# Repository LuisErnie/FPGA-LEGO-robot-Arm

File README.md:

# FPGA-LEGO-robot-Arm
El presente proyecto consiste en el desarrollo de un sistema de control lógico para un robot manipulador de 4 ejes que permita manipular cada uno de forma independiente. El controlador propuesto es implementado en una **FPGA Altera Cyclone V 5CSEMA5F31C6** integrado en la tarjeta **DE1-SOC** de Terasic junto con una tarjeta diseñada para la lectura de las señales de entrada y control de las señales de potencia para los motores, se utilizan optoaisladores para la separación de la tierra de potencia y tierra lógica.
La implementación del código en VHDL permite la jerarquización de bloques de código que cumplan cada una de las funciones UART, PWM, multiplexor, control de motores, etc. requeridos por el proyecto.

El sistema desarrollo consiste en una tarjeta de interfaz para la FPGA y un panel de control para el operador.

El manipulador fue construido con un Kit de LEGO Mindstorms NXT con 4 grados de libertad cada uno controlado por una implementación independiente en la FPGA, esto para demostrar las ventajas de implementar controladores multieje en una FPGA

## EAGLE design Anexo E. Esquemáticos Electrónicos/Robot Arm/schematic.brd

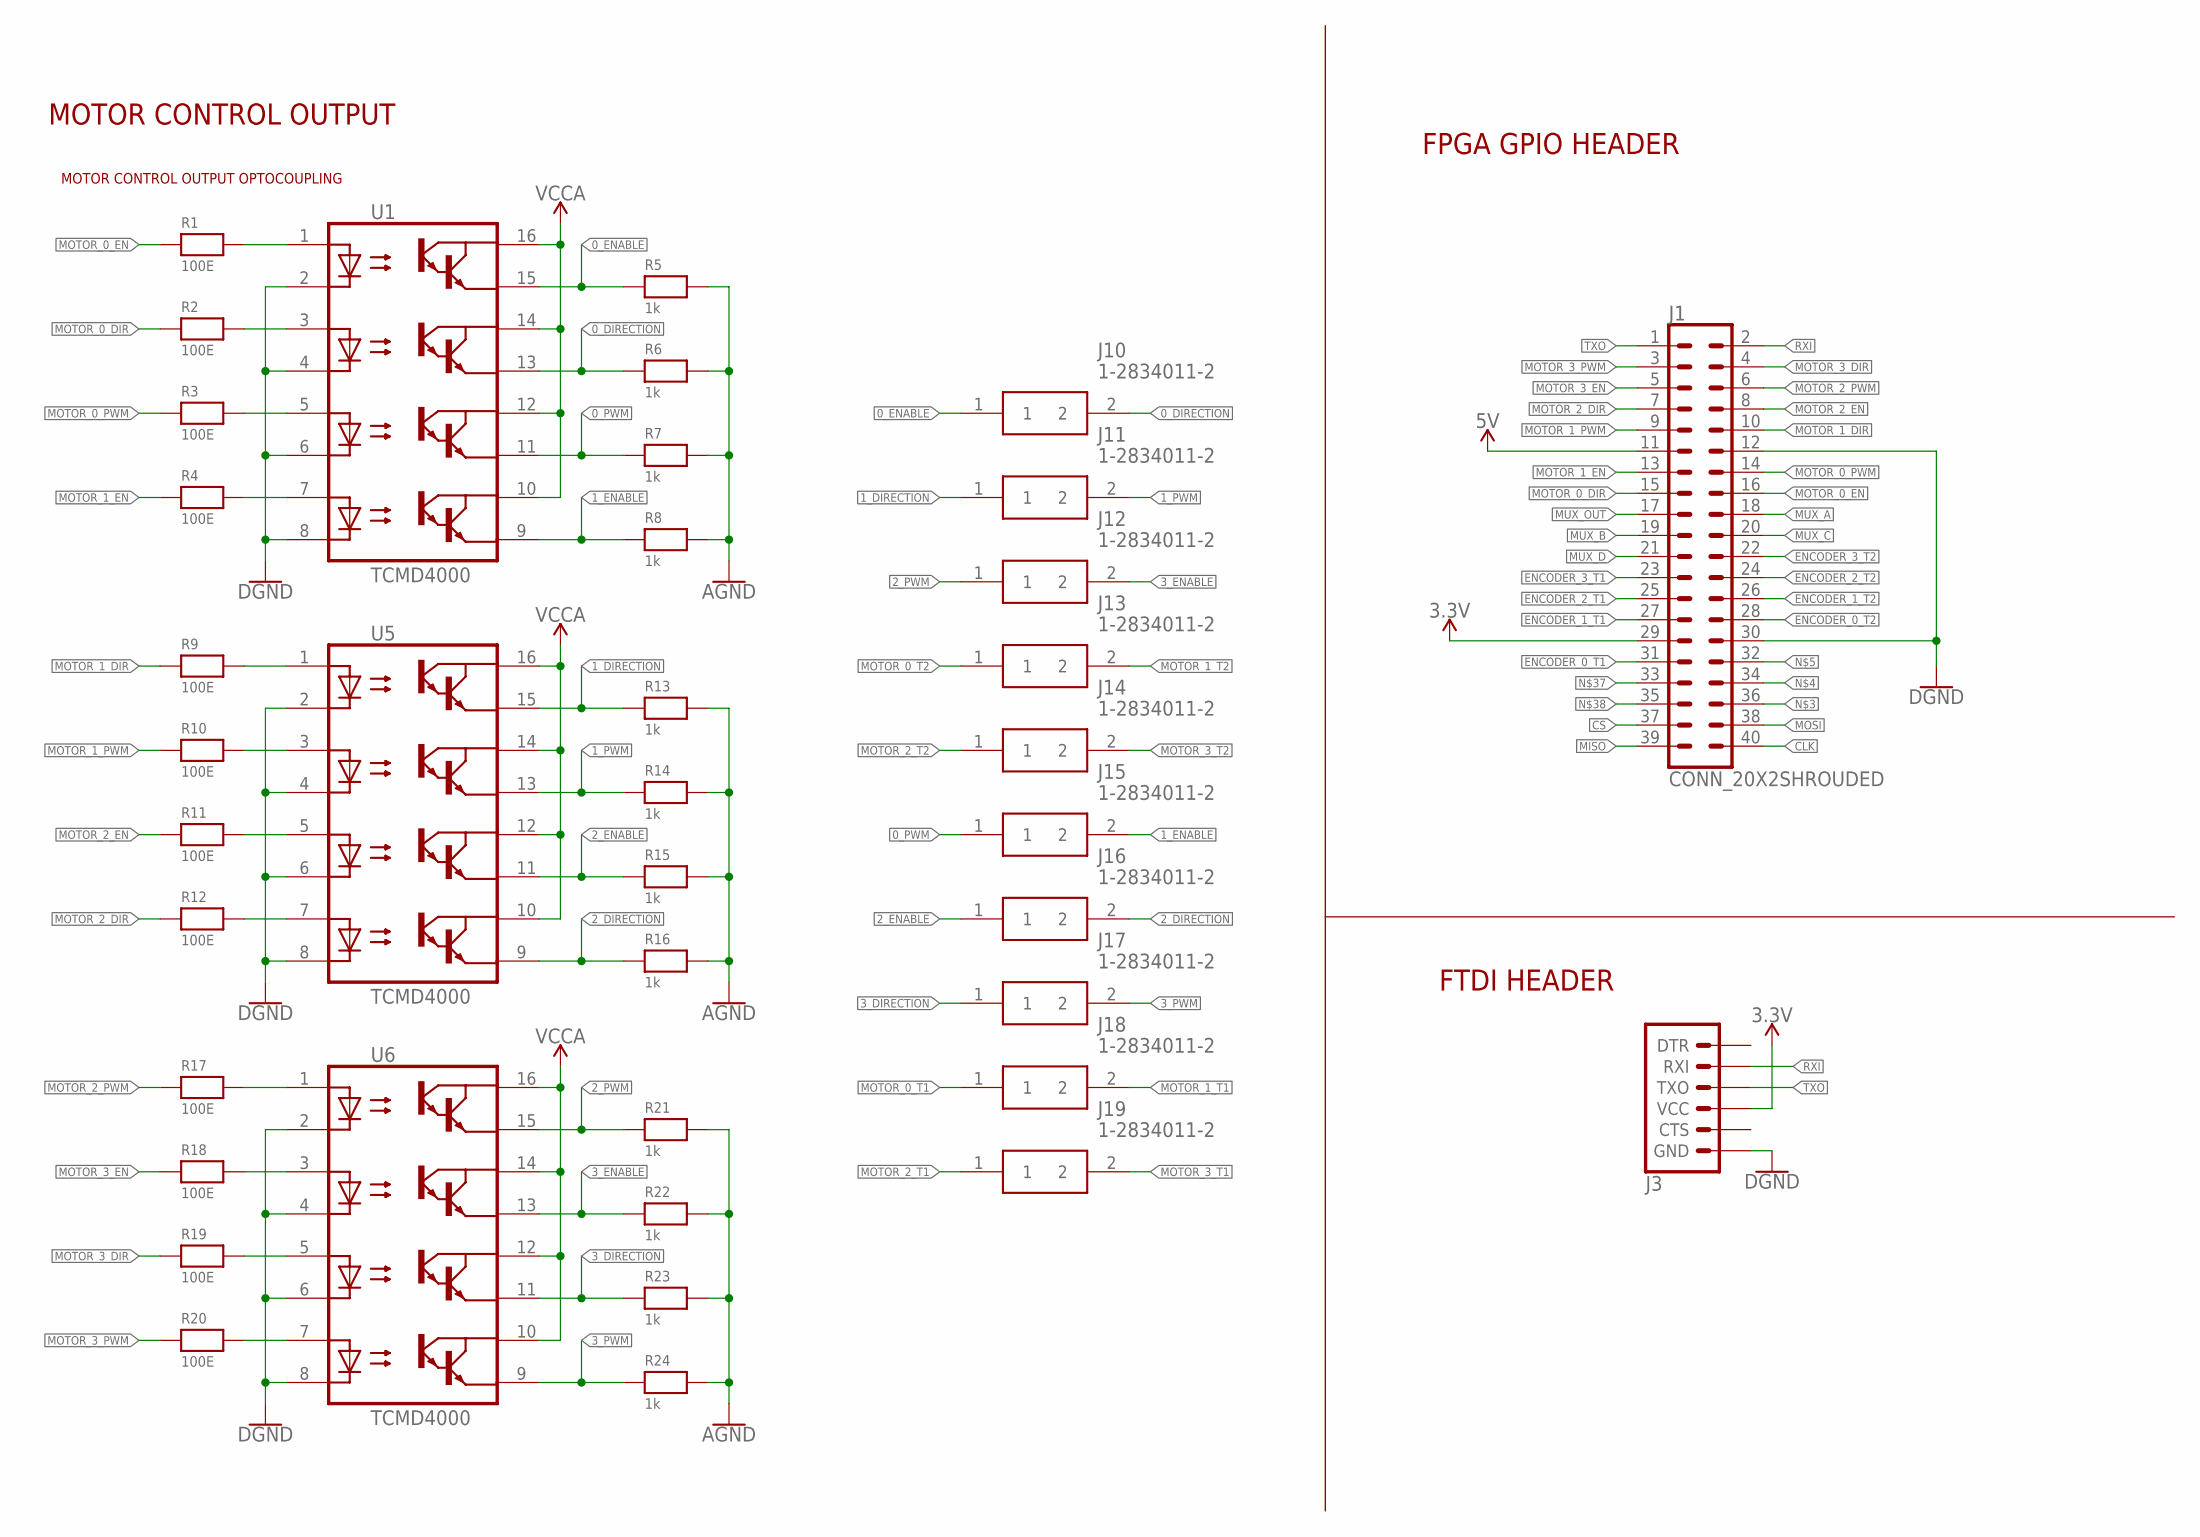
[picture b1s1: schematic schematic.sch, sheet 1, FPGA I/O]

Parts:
J1: CONN_20X2SHROUDED; 2X20_SHROUDED
J3: 6_PIN_SERIAL_TARGET; 1X06
J10, J11, J12, J13, J14, J15, J16, J17, J18, J19: 1-2834011-2; 128340112
R1, R2, R3, R4, R9, R10, R11, R12, R17, R18, R19, R20: 100E; 0805_NOTHERMALS
R5, R6, R7, R8, R13, R14, R15, R16, R21, R22, R23, R24: 1k; 0805_NOTHERMALS
U1, U5, U6: TCMD4000; SOIC127P686X201-16N

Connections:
0_DIRECTION: J10.2, R6.1, U1.13 (E2)
0_ENABLE: J10.1, R5.1, U1.15 (E1)
0_PWM: J15.1, R7.1, U1.11 (E3)
1_DIRECTION: J11.1, R13.1, U5.15 (E1)
1_ENABLE: J15.2, R8.1, U1.9 (E4)
1_PWM: J11.2, R14.1, U5.13 (E2)
2_DIRECTION: J16.2, R16.1, U5.9 (E4)
2_ENABLE: J16.1, R15.1, U5.11 (E3)
2_PWM: J12.1, R21.1, U6.15 (E1)
3.3V: J1.29, J3.4 (VCC); also elsewhere on the board
3_DIRECTION: J17.1, R23.1, U6.11 (E3)
3_ENABLE: J12.2, R22.1, U6.13 (E2)
3_PWM: J17.2, R24.1, U6.9 (E4)
5V: J1.11; also elsewhere on the board
AGND: R5.2, R6.2, R7.2, R8.2, R13.2, R14.2, R15.2, R16.2, R21.2, R22.2, R23.2, R24.2; also elsewhere on the board
CLK: J1.40; also elsewhere on the board
CS: J1.37; also elsewhere on the board
ENCODER_0_T1: J1.31; also elsewhere on the board
ENCODER_0_T2: J1.28; also elsewhere on the board
ENCODER_1_T1: J1.27; also elsewhere on the board
ENCODER_1_T2: J1.26; also elsewhere on the board
ENCODER_2_T1: J1.25; also elsewhere on the board
ENCODER_2_T2: J1.24; also elsewhere on the board
ENCODER_3_T1: J1.23; also elsewhere on the board
ENCODER_3_T2: J1.22; also elsewhere on the board
GND: J1.12, J1.30, J3.6 (GND), U1.2 (C1), U1.4 (C2), U1.6 (C3), U1.8 (C4), U5.2 (C1), U5.4 (C2), U5.6 (C3), U5.8 (C4), U6.2 (C1), U6.4 (C2), U6.6 (C3), U6.8 (C4); also elsewhere on the board
MISO: J1.39; also elsewhere on the board
MOSI: J1.38; also elsewhere on the board
MOTOR_0_DIR: J1.15, R2.1
MOTOR_0_EN: J1.16, R1.1
MOTOR_0_PWM: J1.14, R3.1
MOTOR_0_T1: J18.1; also elsewhere on the board
MOTOR_0_T2: J13.1; also elsewhere on the board
MOTOR_1_DIR: J1.10, R9.1
MOTOR_1_EN: J1.13, R4.1
MOTOR_1_PWM: J1.9, R10.1
MOTOR_1_T1: J18.2; also elsewhere on the board
MOTOR_1_T2: J13.2; also elsewhere on the board
MOTOR_2_DIR: J1.7, R12.1
MOTOR_2_EN: J1.8, R11.1
MOTOR_2_PWM: J1.6, R17.1
MOTOR_2_T1: J19.1; also elsewhere on the board
MOTOR_2_T2: J14.1; also elsewhere on the board
MOTOR_3_DIR: J1.4, R19.1
MOTOR_3_EN: J1.5, R18.1
MOTOR_3_PWM: J1.3, R20.1
MOTOR_3_T1: J19.2; also elsewhere on the board
MOTOR_3_T2: J14.2; also elsewhere on the board
MUX_A: J1.18; also elsewhere on the board
MUX_B: J1.19; also elsewhere on the board
MUX_C: J1.20; also elsewhere on the board
MUX_D: J1.21; also elsewhere on the board
MUX_OUT: J1.17; also elsewhere on the board
unnamed: R1.2, U1.1 (A1)
unnamed: R2.2, U1.3 (A2)
unnamed: R3.2, U1.5 (A3)
unnamed: R4.2, U1.7 (A4)
unnamed: R9.2, U5.1 (A1)
unnamed: R10.2, U5.3 (A2)
unnamed: R11.2, U5.5 (A3)
unnamed: R12.2, U5.7 (A4)
unnamed: R17.2, U6.1 (A1)
unnamed: R18.2, U6.3 (A2)
unnamed: R19.2, U6.5 (A3)
unnamed: R20.2, U6.7 (A4)
RXI: J1.2, J3.2 (RXI)
TXO: J1.1, J3.3 (TXO)
VCCA: U1.10 (CO4), U1.12 (CO3), U1.14 (CO2), U1.16 (CO1), U5.10 (CO4), U5.12 (CO3), U5.14 (CO2), U5.16 (CO1), U6.10 (CO4), U6.12 (CO3), U6.14 (CO2), U6.16 (CO1); also elsewhere on the board

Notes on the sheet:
MOTOR CONTROL OUTPUT
MOTOR CONTROL OUTPUT OPTOCOUPLING
FPGA GPIO HEADER
FTDI HEADER

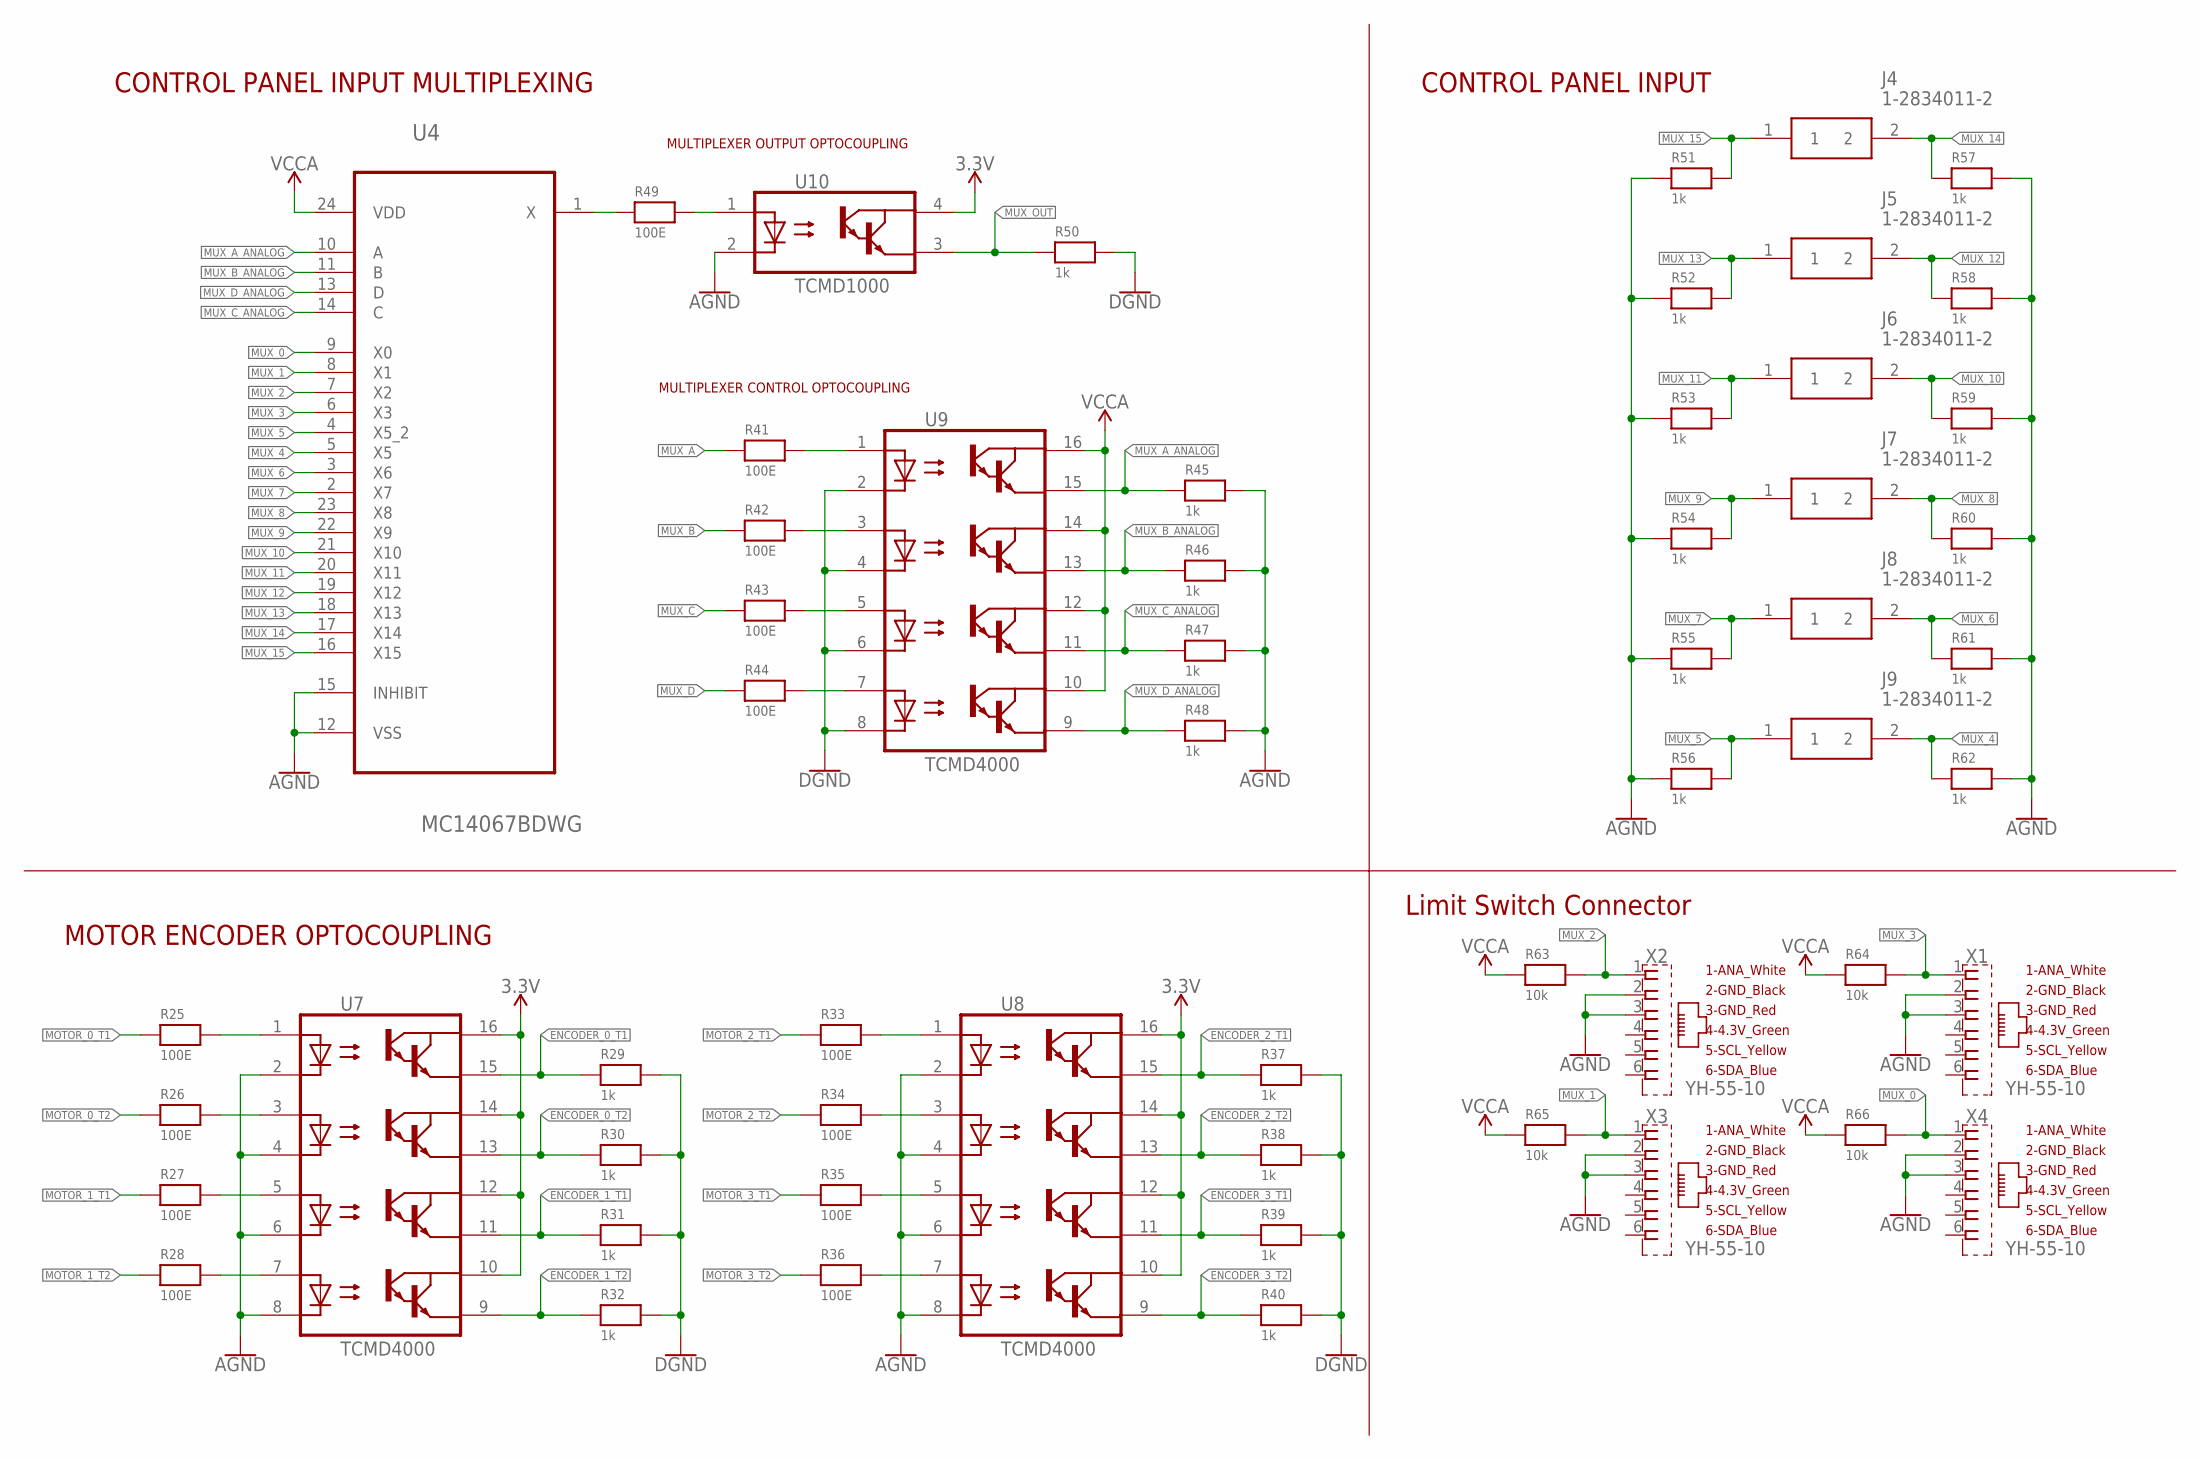
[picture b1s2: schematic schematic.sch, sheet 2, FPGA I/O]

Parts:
J4, J5, J6, J7, J8, J9: 1-2834011-2; 128340112
R25, R26, R27, R28, R33, R34, R35, R36, R41, R42, R43, R44, R49: 100E; 0805_NOTHERMALS
R29, R30, R31, R32, R37, R38, R39, R40, R45, R46, R47, R48, R50, R51, R52, R53, R54, R55, R56, R57, R58, R59, R60, R61, R62: 1k; 0805_NOTHERMALS
R63, R64, R65, R66: 10k; 0805_NOTHERMALS
U4: MC14067BDWG; SOIC127P1030X265-24N
U7, U8, U9: TCMD4000; SOIC127P686X201-16N
U10: TCMD1000; SOIC254P695X210-4N
X1, X2, X3, X4: YH-55-10

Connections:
3.3V: U7.10 (CO4), U7.12 (CO3), U7.14 (CO2), U7.16 (CO1), U8.10 (CO4), U8.12 (CO3), U8.14 (CO2), U8.16 (CO1), U10.4 (CO1); also elsewhere on the board
AGND: R45.2, R46.2, R47.2, R48.2, R51.1, R52.1, R53.1, R54.1, R55.1, R56.1, R57.2, R58.2, R59.2, R60.2, R61.2, R62.2, U4.12 (VSS), U4.15 (INHIBIT), U7.2 (C1), U7.4 (C2), U7.6 (C3), U7.8 (C4), U8.2 (C1), U8.4 (C2), U8.6 (C3), U8.8 (C4), U10.2 (C1), X1.2 (2_GND_BLACK), X1.3 (3_GND_RED), X2.2 (2_GND_BLACK), X2.3 (3_GND_RED), X3.2 (2_GND_BLACK), X3.3 (3_GND_RED), X4.2 (2_GND_BLACK), X4.3 (3_GND_RED); also elsewhere on the board
ENCODER_0_T1: R29.1, U7.15 (E1); also elsewhere on the board
ENCODER_0_T2: R30.1, U7.13 (E2); also elsewhere on the board
ENCODER_1_T1: R31.1, U7.11 (E3); also elsewhere on the board
ENCODER_1_T2: R32.1, U7.9 (E4); also elsewhere on the board
ENCODER_2_T1: R37.1, U8.15 (E1); also elsewhere on the board
ENCODER_2_T2: R38.1, U8.13 (E2); also elsewhere on the board
ENCODER_3_T1: R39.1, U8.11 (E3); also elsewhere on the board
ENCODER_3_T2: R40.1, U8.9 (E4); also elsewhere on the board
GND: R29.2, R30.2, R31.2, R32.2, R37.2, R38.2, R39.2, R40.2, R50.2, U9.2 (C1), U9.4 (C2), U9.6 (C3), U9.8 (C4); also elsewhere on the board
MOTOR_0_T1: R25.1; also elsewhere on the board
MOTOR_0_T2: R26.1; also elsewhere on the board
MOTOR_1_T1: R27.1; also elsewhere on the board
MOTOR_1_T2: R28.1; also elsewhere on the board
MOTOR_2_T1: R33.1; also elsewhere on the board
MOTOR_2_T2: R34.1; also elsewhere on the board
MOTOR_3_T1: R35.1; also elsewhere on the board
MOTOR_3_T2: R36.1; also elsewhere on the board
MUX_0: R66.2, U4.9 (X0), X4.1 (1_ANA_WHITE)
MUX_1: R65.2, U4.8 (X1), X3.1 (1_ANA_WHITE)
MUX_2: R63.2, U4.7 (X2), X2.1 (1_ANA_WHITE)
MUX_3: R64.2, U4.6 (X3), X1.1 (1_ANA_WHITE)
MUX_4: J9.2, R62.1, U4.5 (X5)
MUX_5: J9.1, R56.2, U4.4 (X5_2)
MUX_6: J8.2, R61.1, U4.3 (X6)
MUX_7: J8.1, R55.2, U4.2 (X7)
MUX_8: J7.2, R60.1, U4.23 (X8)
MUX_9: J7.1, R54.2, U4.22 (X9)
MUX_10: J6.2, R59.1, U4.21 (X10)
MUX_11: J6.1, R53.2, U4.20 (X11)
MUX_12: J5.2, R58.1, U4.19 (X12)
MUX_13: J5.1, R52.2, U4.18 (X13)
MUX_14: J4.2, R57.1, U4.17 (X14)
MUX_15: J4.1, R51.2, U4.16 (X15)
MUX_A: R41.1; also elsewhere on the board
MUX_A_ANALOG: R45.1, U4.10 (A), U9.15 (E1)
MUX_B: R42.1; also elsewhere on the board
MUX_B_ANALOG: R46.1, U4.11 (B), U9.13 (E2)
MUX_C: R43.1; also elsewhere on the board
MUX_C_ANALOG: R47.1, U4.14 (C), U9.11 (E3)
MUX_D: R44.1; also elsewhere on the board
MUX_D_ANALOG: R48.1, U4.13 (D), U9.9 (E4)
MUX_OUT: R50.1, U10.3 (E1); also elsewhere on the board
unnamed: R33.2, U8.1 (A1)
unnamed: R34.2, U8.3 (A2)
unnamed: R35.2, U8.5 (A3)
unnamed: R49.1, U4.1 (X)
unnamed: R36.2, U8.7 (A4)
unnamed: R49.2, U10.1 (A1)
unnamed: R41.2, U9.1 (A1)
unnamed: R25.2, U7.1 (A1)
unnamed: R26.2, U7.3 (A2)
unnamed: R27.2, U7.5 (A3)
unnamed: R28.2, U7.7 (A4)
unnamed: R42.2, U9.3 (A2)
unnamed: R43.2, U9.5 (A3)
unnamed: R44.2, U9.7 (A4)
VCCA: R63.1, R64.1, R65.1, R66.1, U4.24 (VDD), U9.10 (CO4), U9.12 (CO3), U9.14 (CO2), U9.16 (CO1); also elsewhere on the board

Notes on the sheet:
MULTIPLEXER CONTROL OPTOCOUPLING
MULTIPLEXER OUTPUT OPTOCOUPLING
MOTOR ENCODER OPTOCOUPLING
CONTROL PANEL INPUT MULTIPLEXING
CONTROL PANEL INPUT
Limit Switch Connector

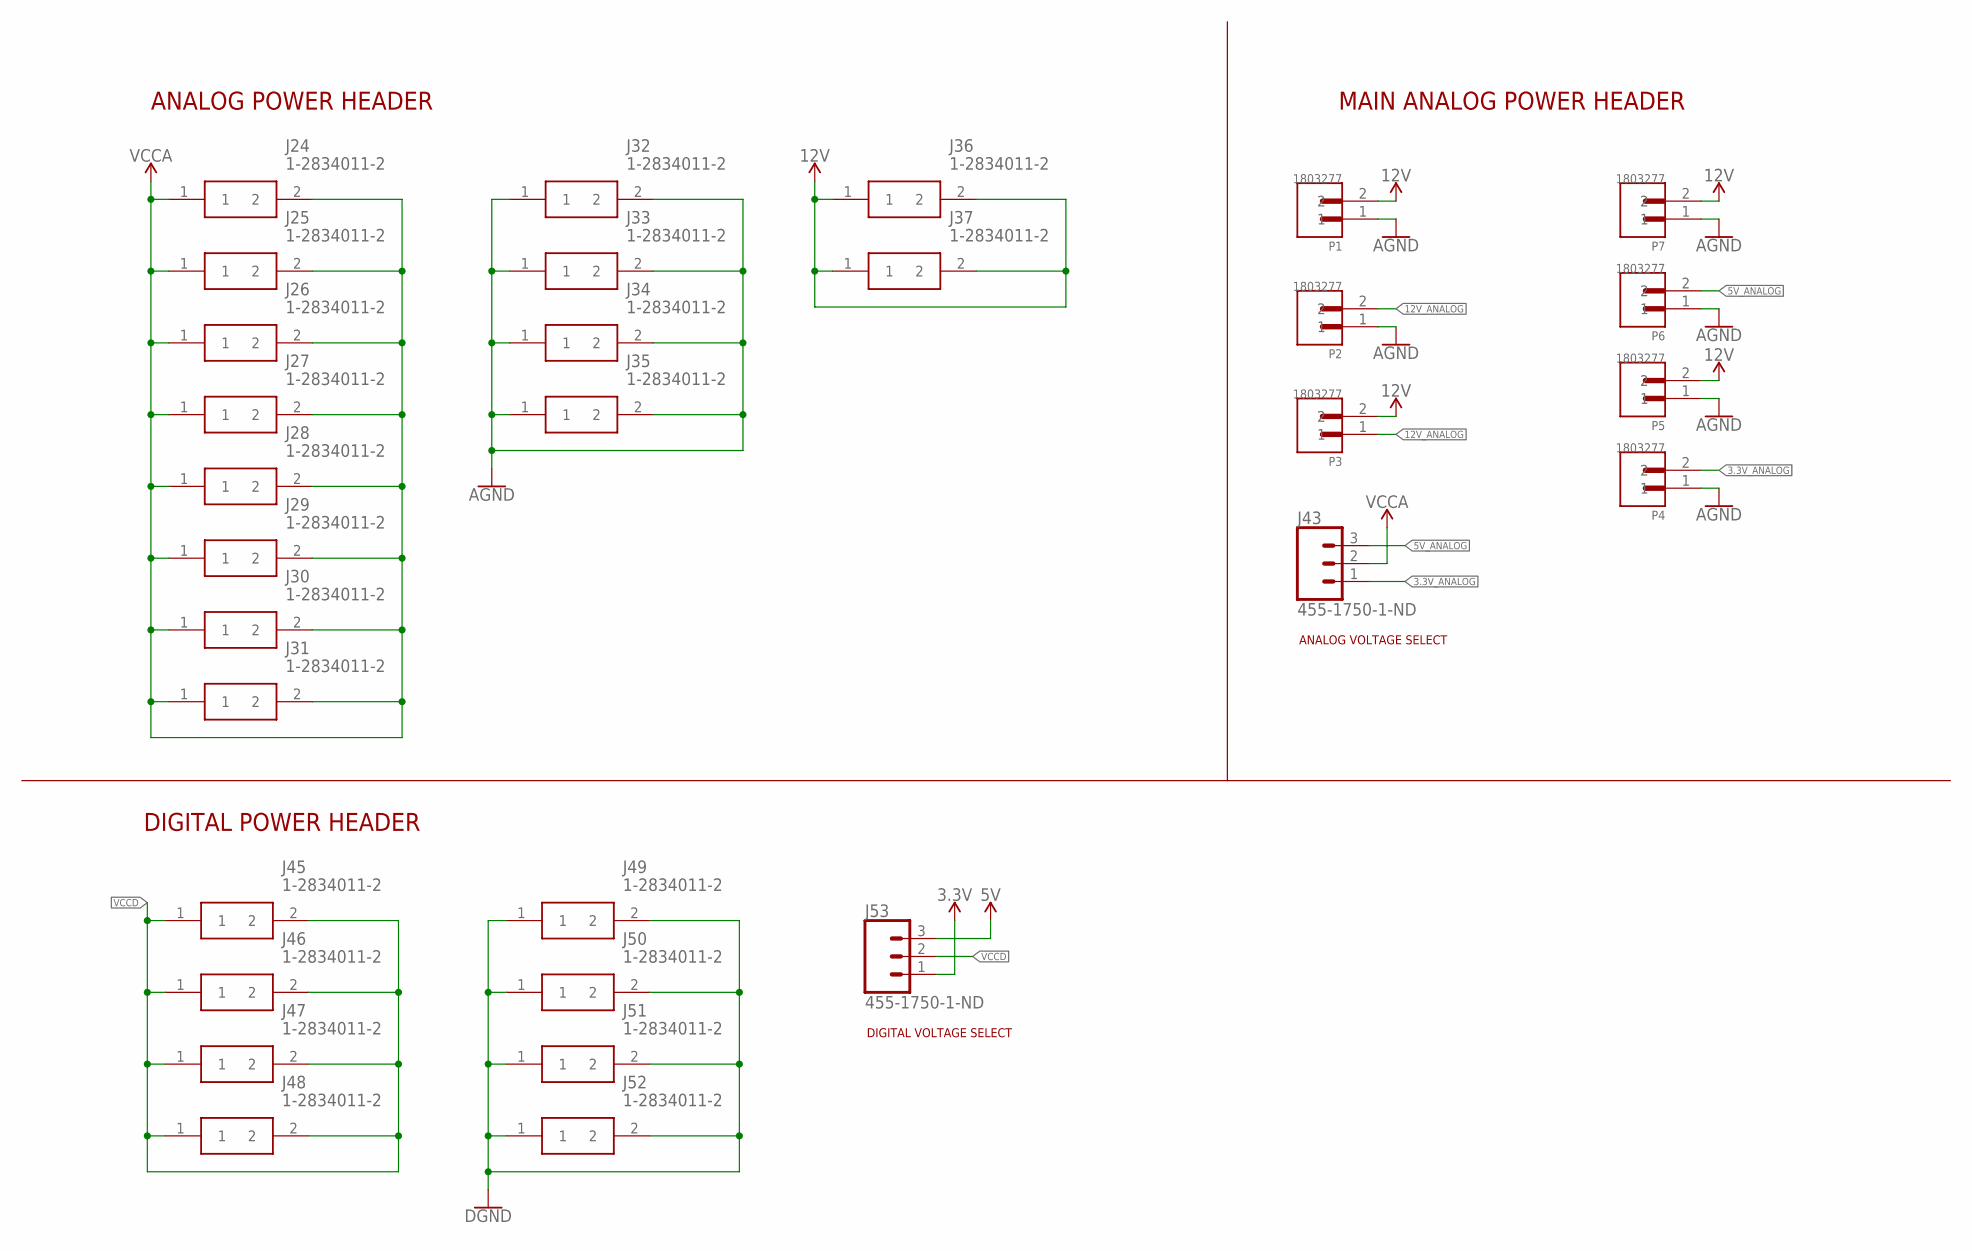
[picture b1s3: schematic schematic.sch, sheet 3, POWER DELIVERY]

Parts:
J24, J25, J26, J27, J28, J29, J30, J31, J32, J33, J34, J35, J36, J37, J45, J46, J47, J48, J49, J50, J51, J52: 1-2834011-2; 128340112
J43, J53: 455-1750-1-ND; 1X03
P1, P2, P3, P4, P5, P6, P7: 1803277; PHOENIX_1803277

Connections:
3.3V: J53.1; also elsewhere on the board
3.3V_ANALOG: J43.1, P4.2
5V: J53.3; also elsewhere on the board
5V_ANALOG: J43.3, P6.2
12V: J36.1, J36.2, J37.1, J37.2, P1.2, P3.2, P5.2, P7.2
12V_ANALOG: P2.2, P3.1
AGND: J32.1, J32.2, J33.1, J33.2, J34.1, J34.2, J35.1, J35.2, P1.1, P2.1, P4.1, P5.1, P6.1, P7.1; also elsewhere on the board
GND: J49.1, J49.2, J50.1, J50.2, J51.1, J51.2, J52.1, J52.2; also elsewhere on the board
VCCA: J24.1, J24.2, J25.1, J25.2, J26.1, J26.2, J27.1, J27.2, J28.1, J28.2, J29.1, J29.2, J30.1, J30.2, J31.1, J31.2, J43.2; also elsewhere on the board
VCCD: J45.1, J45.2, J46.1, J46.2, J47.1, J47.2, J48.1, J48.2, J53.2

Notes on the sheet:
ANALOG POWER HEADER
DIGITAL POWER HEADER
MAIN ANALOG POWER HEADER
DIGITAL VOLTAGE SELECT
ANALOG VOLTAGE SELECT

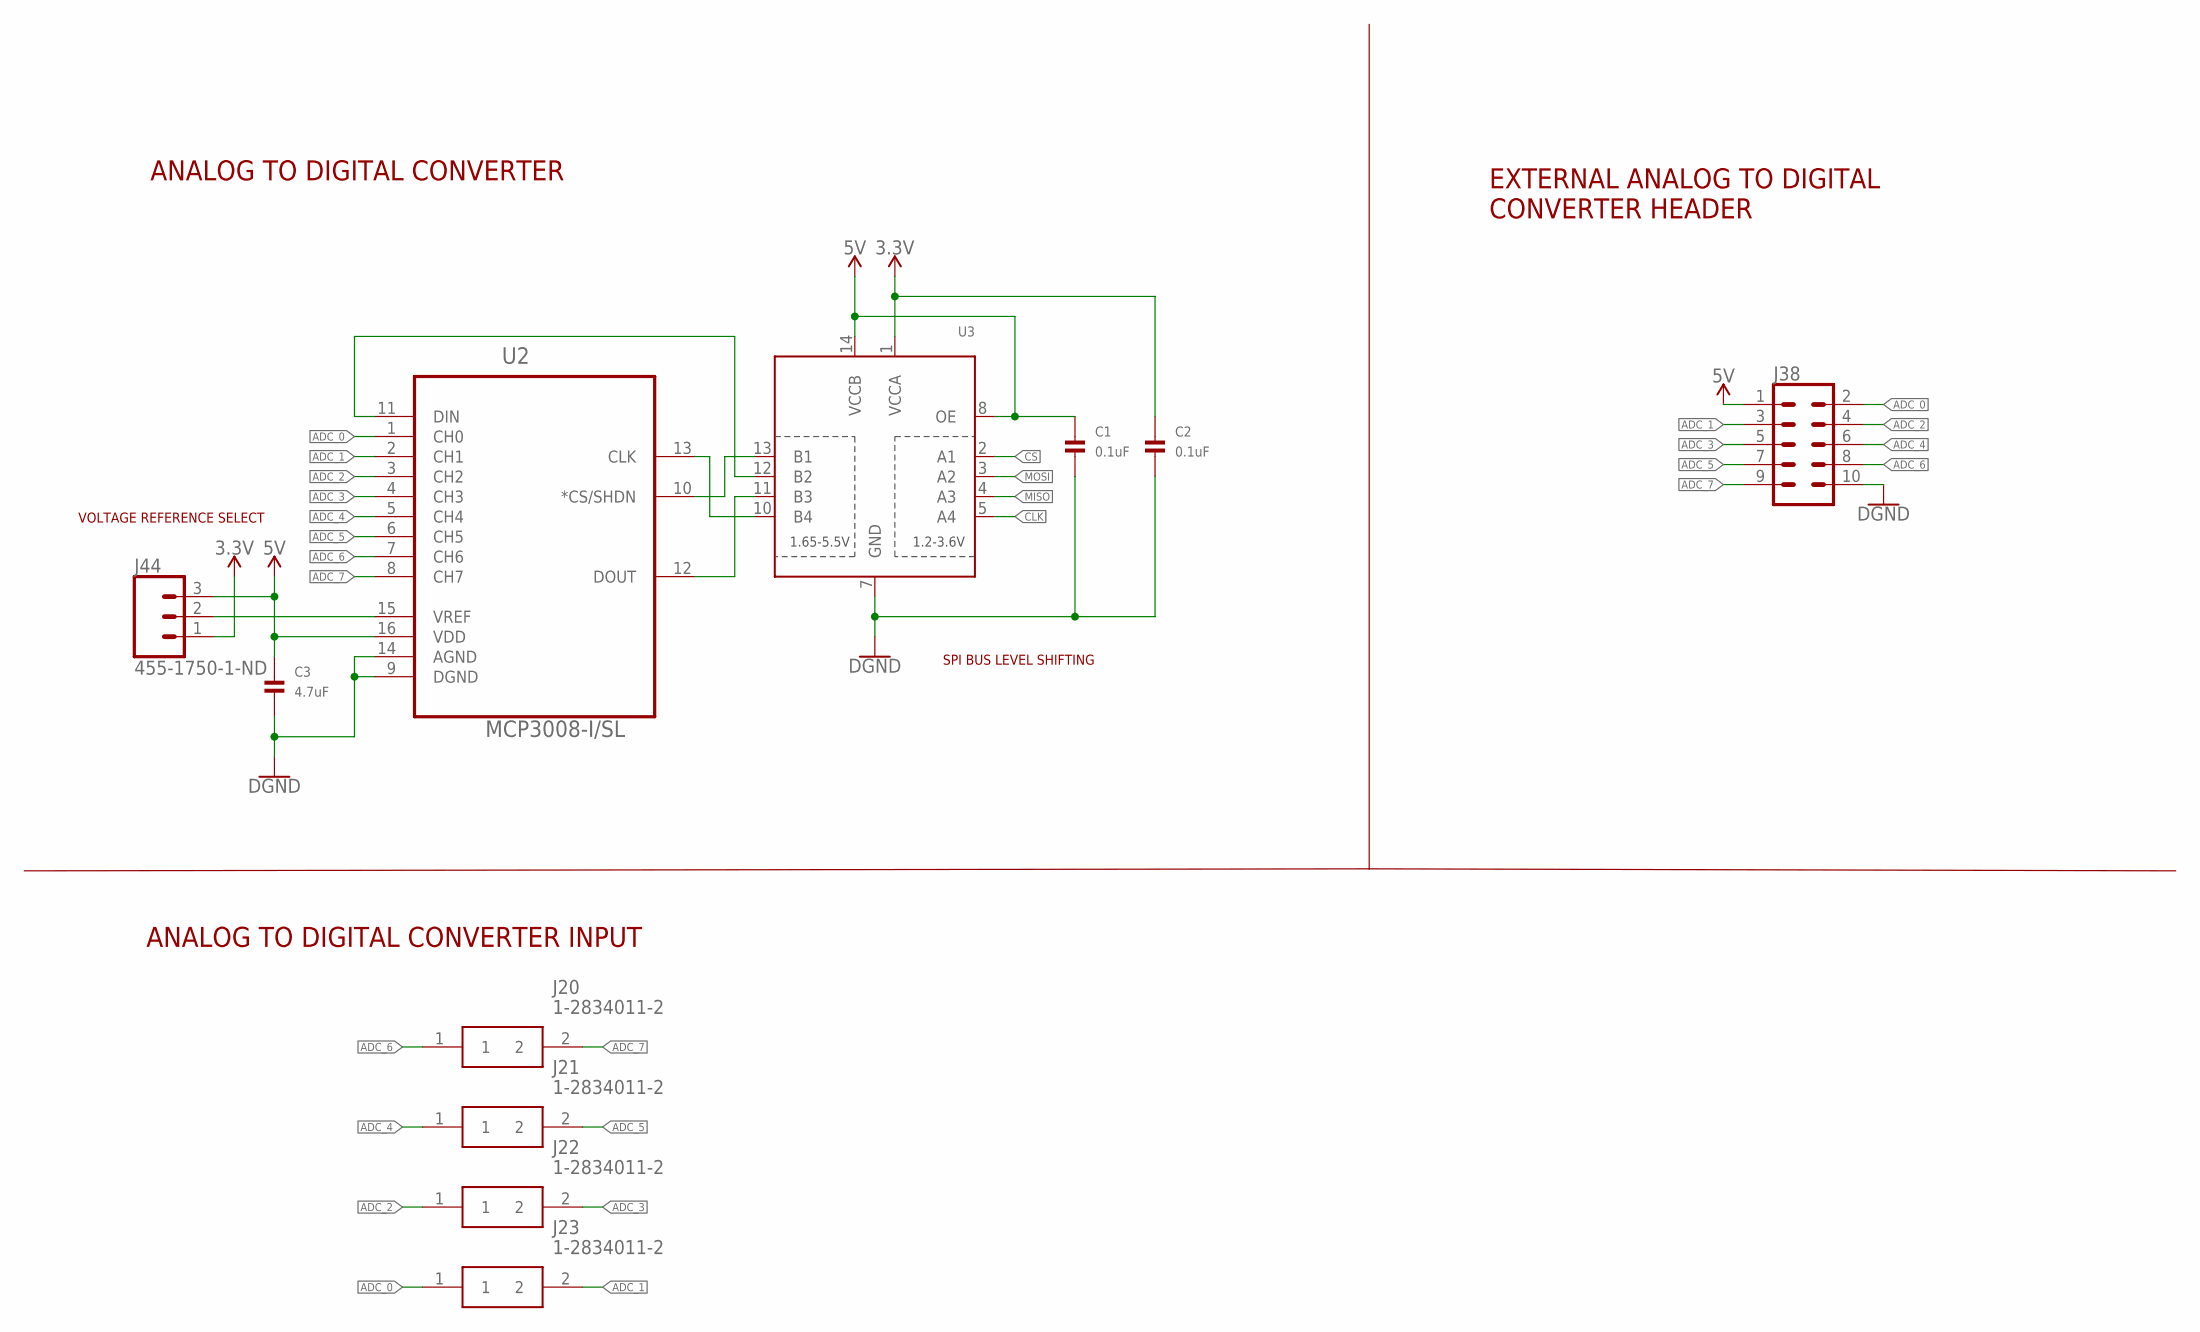
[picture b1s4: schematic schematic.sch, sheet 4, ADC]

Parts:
C1, C2: 0.1uF; 0805_NOTHERMALS
C3: 4.7uF; 0805_NOTHERMALS
J20, J21, J22, J23: 1-2834011-2; 128340112
J38: CONN_05X2SHD; 2X5-SHROUDED
J44: 455-1750-1-ND; 1X03
U2: MCP3008-I/SL; SOIC127P600X175-16N
U3: TXB0104PWR; TSSOP14

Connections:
3.3V: C2.1, J44.1, U3.1 (VCCA); also elsewhere on the board
5V: C1.1, C3.1, J38.1, J44.3, U2.16 (VDD), U3.8 (OE), U3.14 (VCCB); also elsewhere on the board
ADC_0: J23.1, J38.2, U2.1 (CH0)
ADC_1: J23.2, J38.3, U2.2 (CH1)
ADC_2: J22.1, J38.4, U2.3 (CH2)
ADC_3: J22.2, J38.5, U2.4 (CH3)
ADC_4: J21.1, J38.6, U2.5 (CH4)
ADC_5: J21.2, J38.7, U2.6 (CH5)
ADC_6: J20.1, J38.8, U2.7 (CH6)
ADC_7: J20.2, J38.9, U2.8 (CH7)
CLK: U3.5 (A4); also elsewhere on the board
CS: U3.2 (A1); also elsewhere on the board
GND: C1.2, C2.2, C3.2, J38.10, U2.9 (DGND), U2.14 (AGND), U3.7 (GND); also elsewhere on the board
MISO: U3.4 (A3); also elsewhere on the board
MOSI: U3.3 (A2); also elsewhere on the board
unnamed: U2.10 (*CS/SHDN), U3.13 (B1)
unnamed: U2.12 (DOUT), U3.11 (B3)
unnamed: U2.13 (CLK), U3.10 (B4)
unnamed: U2.11 (DIN), U3.12 (B2)
unnamed: J44.2, U2.15 (VREF)

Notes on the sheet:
ANALOG TO DIGITAL CONVERTER
ANALOG TO DIGITAL CONVERTER INPUT
EXTERNAL ANALOG TO DIGITAL CONVERTER HEADER
VOLTAGE REFERENCE SELECT
SPI BUS LEVEL SHIFTING

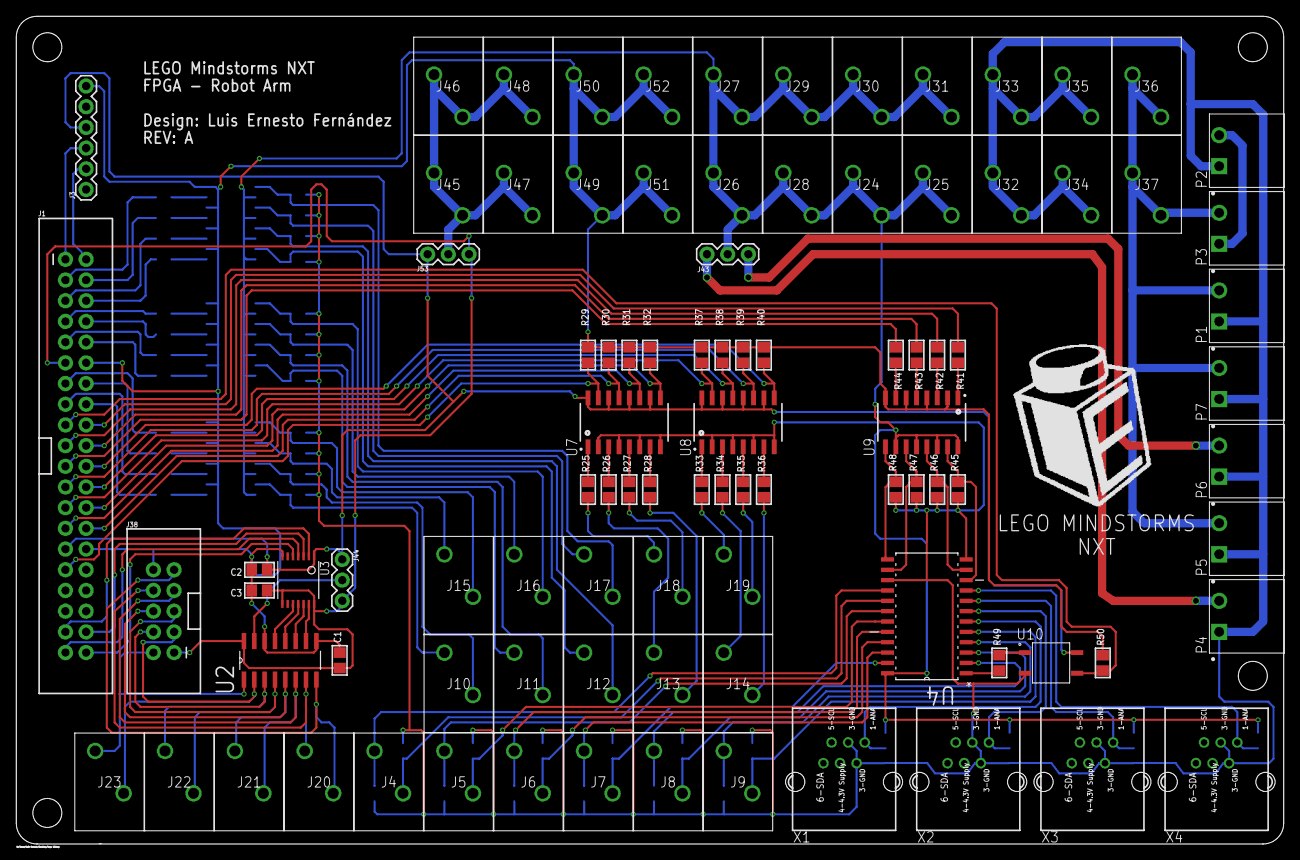
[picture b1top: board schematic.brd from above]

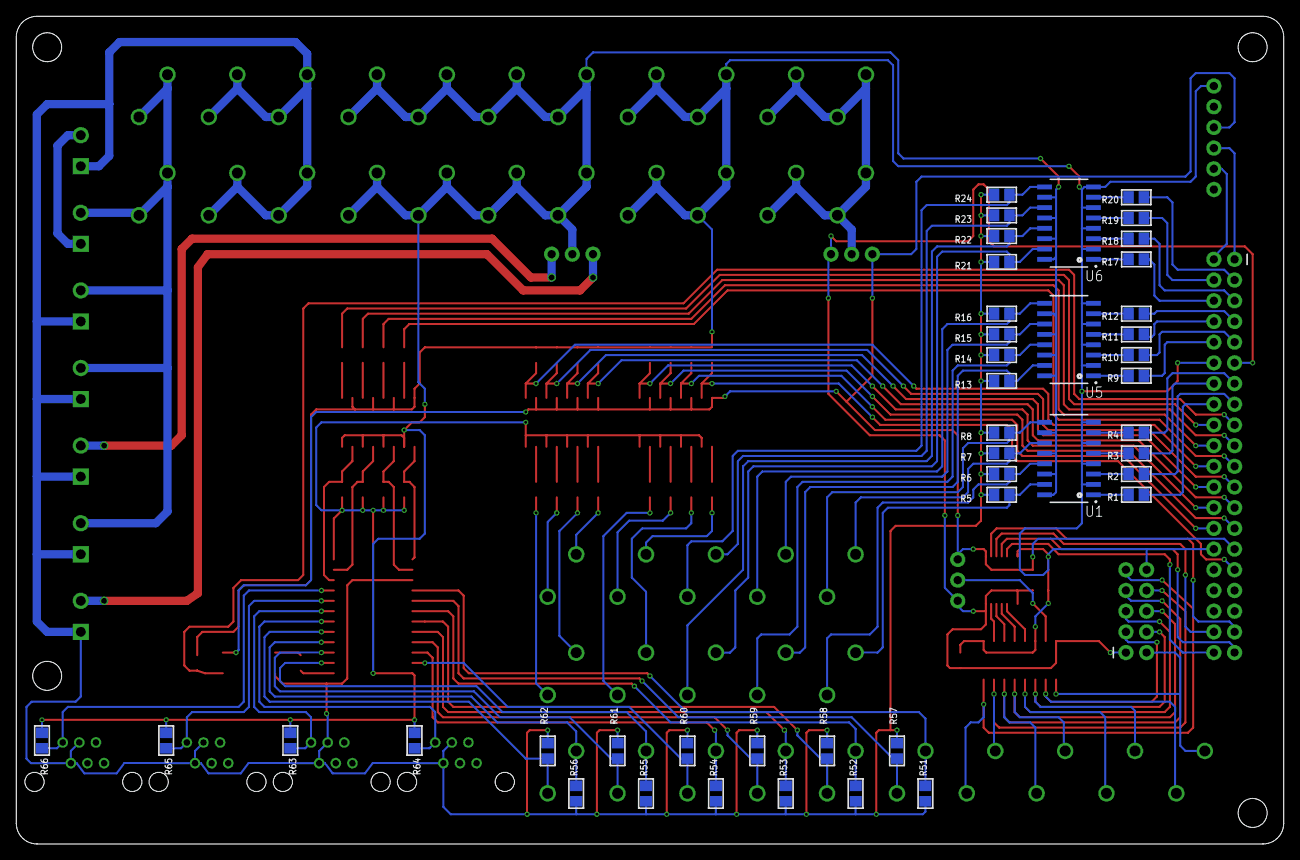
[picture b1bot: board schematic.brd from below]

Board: 2 copper layers, 155.6 x 101.6 mm, 138 parts (43 on the bottom side), 120 nets.

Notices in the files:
parts and their libraries:
microbuilder: This work is placed in the public domain, and may be freely used for commercial and non-commercial work with the following conditions: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
SparkFun-Connectors: Licensing: Creative Commons ShareAlike 4.0 International - https://creativecommons.org/licenses/by-sa/4.0
